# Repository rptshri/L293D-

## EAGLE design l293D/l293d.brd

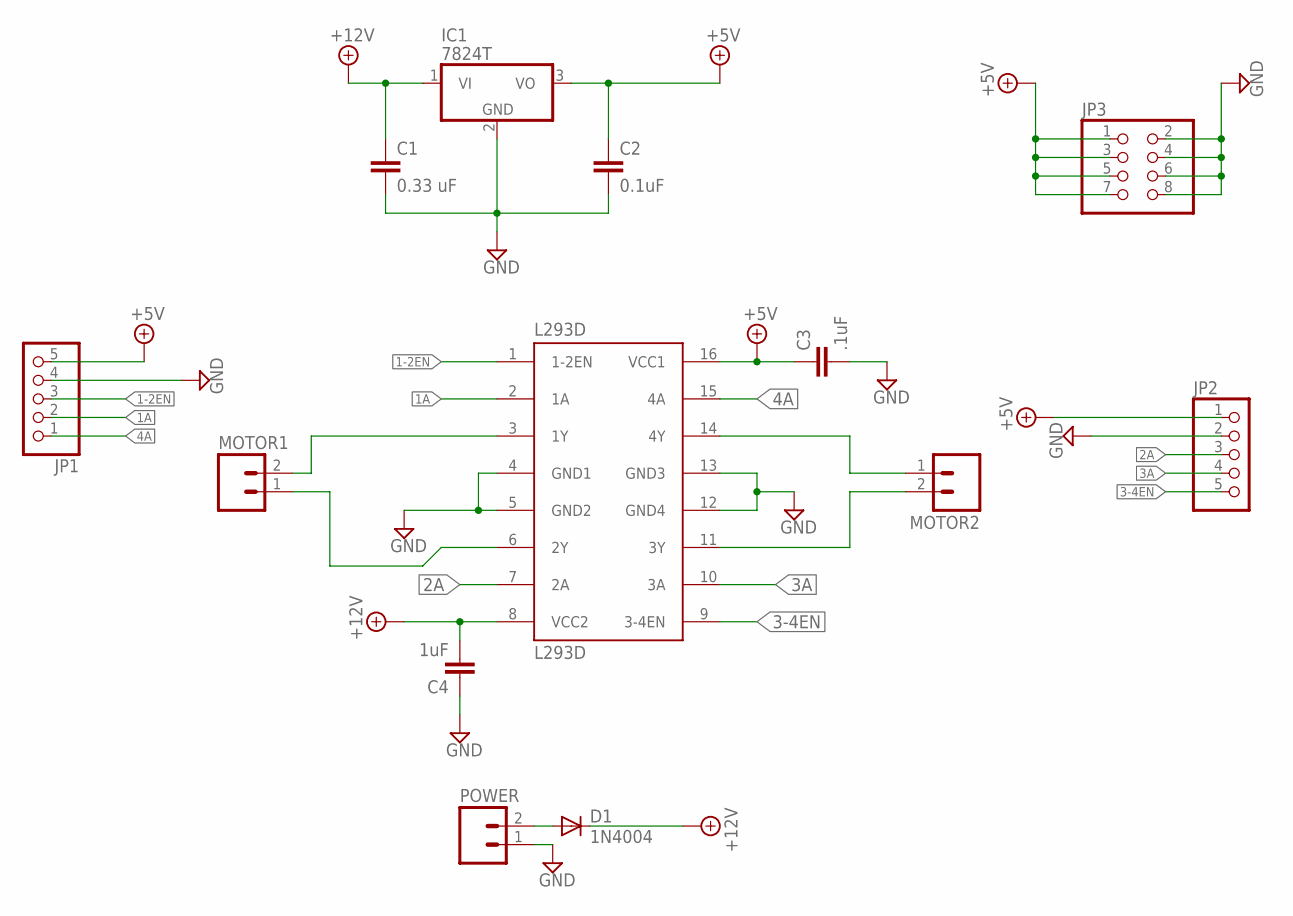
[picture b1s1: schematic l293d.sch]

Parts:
C1: 0.33 uF; C050-024X044
C2: 0.1uF; C050-024X044
C3: .1uF; C050-024X044
C4: 1uF; C050-024X044
D1: 1N4004; DO41-10
IC1: 7824T; TO220H
JP1, JP2: PINHD-1X5; 1X05
JP3: PINHD-2X4; 2X04
L293D: L293D; DIL16
MOTOR1, MOTOR2: M023.5MM-NO_SILK; SCREWTERMINAL-3.5MM-2-NS
POWER: M023.5MM-NO_SILK; SCREWTERMINAL-3.5MM-2-NS

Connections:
1-2EN: JP1.3, L293D.1 (1-2EN)
1A: JP1.2, L293D.2 (1A)
2A: JP2.3, L293D.7 (2A)
3-4EN: JP2.5, L293D.9 (3-4EN)
3A: JP2.4, L293D.10 (3A)
4A: JP1.1, L293D.15 (4A)
+5V: C2.1, C3.1, IC1.3 (VO), JP1.5, JP2.1, JP3.1, JP3.3, JP3.5, JP3.7, L293D.16 (VCC1)
+12V: C1.1, C4.2, D1.C, IC1.1 (VI), L293D.8 (VCC2)
GND: C1.2, C2.2, C3.2, C4.1, IC1.2 (GND), JP1.4, JP2.2, JP3.2, JP3.4, JP3.6, JP3.8, L293D.4 (GND1), L293D.5 (GND2), L293D.12 (GND4), L293D.13 (GND3), POWER.1
unnamed: L293D.14 (4Y), MOTOR2.1
unnamed: L293D.3 (1Y), MOTOR1.2
unnamed: L293D.6 (2Y), MOTOR1.1
unnamed: L293D.11 (3Y), MOTOR2.2
unnamed: D1.A, POWER.2

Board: 2 copper layers, 13 parts (0 on the bottom side), 14 nets, no tracks yet.

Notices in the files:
parts and their libraries:
SparkFun-Connectors: Licensing: Creative Commons ShareAlike 4.0 International - https://creativecommons.org/licenses/by-sa/4.0
